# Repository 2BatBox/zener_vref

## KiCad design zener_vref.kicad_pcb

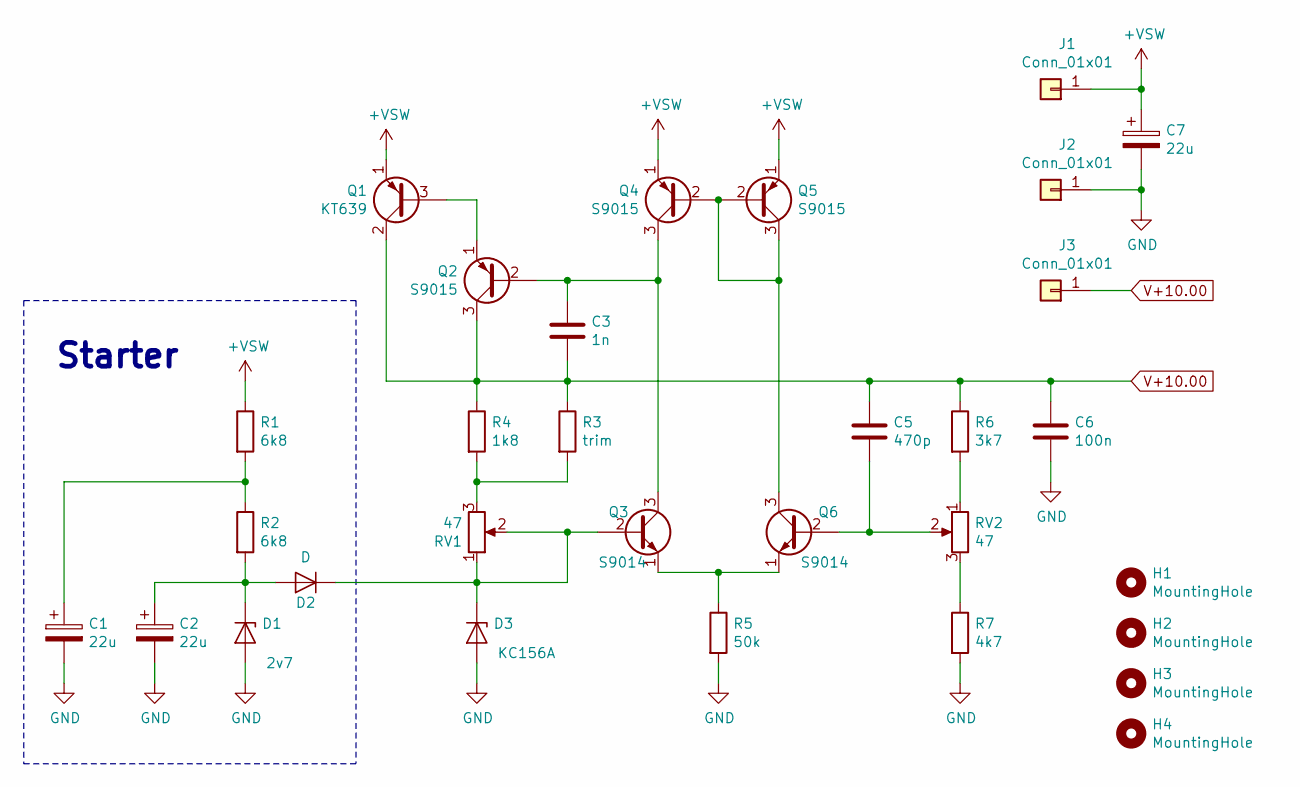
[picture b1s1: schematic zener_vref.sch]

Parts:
C1, C2, C7: 22u; LUT_CP_Radial_D5.0mm_P2.50mm
C3: 1n; LUT_C_Disc_D7.5mm_W2.5mm_P5.00mm
C5: 470p; LUT_C_Disc_D7.5mm_W2.5mm_P5.00mm
C6: 100n; LUT_C_Rect_L10.3mm_W5.0mm_P7.50mm
D1: 2v7; LUT_D_P7.62mm_Horizontal
D2: D; LUT_D_P7.62mm_Horizontal
D3: КС156А; LUT_D_H7.0_W9.0_P30.48_Horizontal
H1, H2, H3, H4: MountingHole; MountingHole_3.2mm_M3
J1, J2, J3: Conn_01x01; LUT_Wire_Clip_2_P2.54mm
Q1: KT639; LUT_TO-126-3_Vertical
Q2, Q4, Q5: S9015; LUT_TO-92
Q3, Q6: S9014; LUT_TO-92
R1, R2: 6k8; LUT_R_L9.9mm_D3.6mm_P12.70mm_Horizontal
R3: trim; LUT_R_L9.9mm_D3.6mm_P12.70mm_Horizontal
R4: 1k8; LUT_R_L9.9mm_D3.6mm_P12.70mm_Horizontal
R5: 50k; LUT_R_L9.9mm_D3.6mm_P12.70mm_Horizontal
R6: 3k7; LUT_R_L9.9mm_D3.6mm_P12.70mm_Horizontal
R7: 4k7; LUT_R_L9.9mm_D3.6mm_P12.70mm_Horizontal
RV1, RV2: 47; LUT_RPot_SP3-38B_Horizontal

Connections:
+VSW: C7.1, J1.1, Q1.1 (E), Q4.1 (E), Q5.1 (E), R1.1
GND: C1.2, C2.2, C6.2, C7.2, D1.2 (A), D3.2 (A), J2.1, R5.2, R7.2
unnamed: C1.1, R1.2, R2.1
unnamed: C2.1, D1.1 (K), D2.2 (A), R2.2
unnamed: C3.1, Q2.2 (B), Q3.3 (C), Q4.3 (C)
unnamed: C5.2, Q6.2 (B), RV2.2
unnamed: D2.1 (K), D3.1 (K), Q3.2 (B), RV1.1, RV1.2
unnamed: Q1.3 (B), Q2.1 (E)
unnamed: Q3.1 (E), Q6.1 (E), R5.1
unnamed: Q4.2 (B), Q5.2 (B), Q5.3 (C), Q6.3 (C)
unnamed: R3.2, R4.2, RV1.3
unnamed: R6.2, RV2.1
unnamed: R7.1, RV2.3
V+10.00: C3.2, C5.1, C6.1, J3.1, Q1.2 (C), Q2.3 (C), R3.1, R4.1, R6.1

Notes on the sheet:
Starter

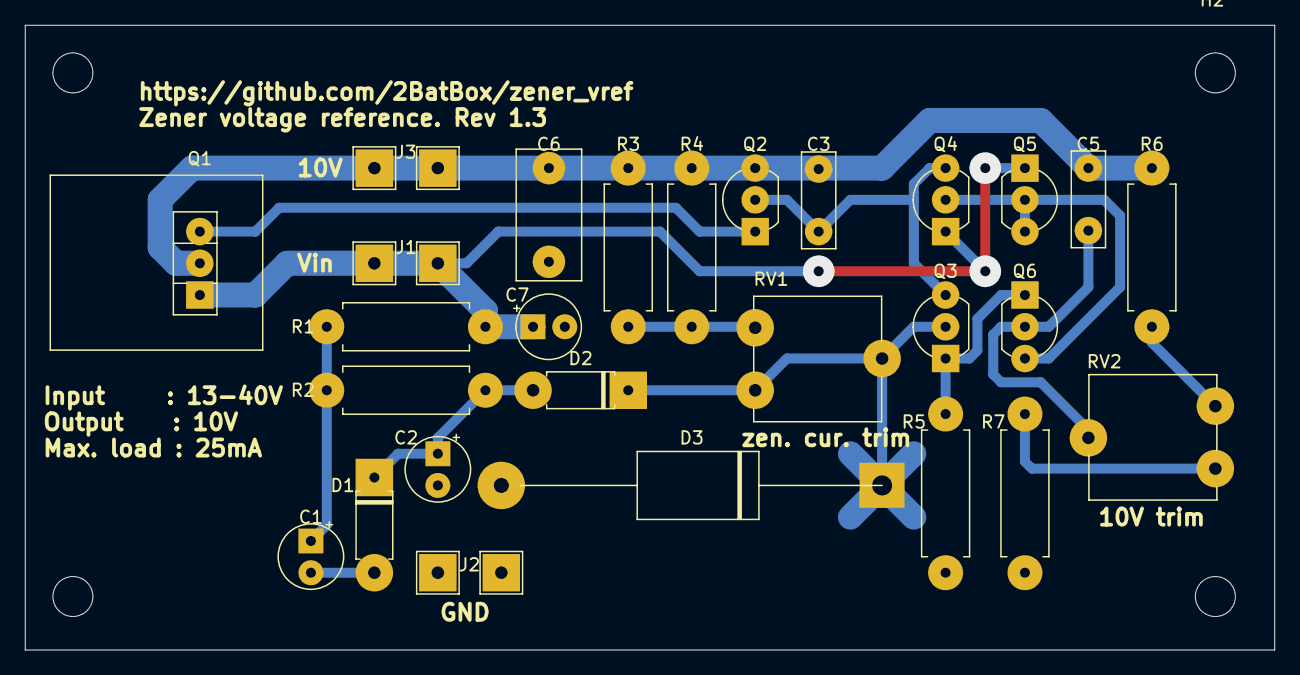
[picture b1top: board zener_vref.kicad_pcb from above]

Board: 2 copper layers, 100.0 x 50.0 mm, 31 parts (0 on the bottom side), 14 nets.

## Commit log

2024-03-19 Version 1.3 : 10v KC156A
